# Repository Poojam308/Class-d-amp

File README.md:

# 🔊 Class-D Audio Pre-Amplifier

A specialized hardware design for a high-efficiency Class-D audio pre-amplifier. This project leverages the precision of KiCad 8.0 to implement a switching amplifier topology, focusing on low-noise signal processing and high-frequency pulse-width modulation (PWM).

## **✨ Features**

* **⚡ Class-D Topology:** Utilizes high-frequency switching for superior efficiency compared to traditional linear amplifiers.
* **🎯 Precision Timing:** Employs a CMOS-based LMC555 timer for stable PWM signal generation.
* **📉 Low-Noise Pre-amplification:** Integrated TL072 JFET-input operational amplifiers for high-fidelity audio signal conditioning.
* **🛡️ Robust Power Stage:** Features IRF540N HEXFET Power MOSFETs for reliable switching and power delivery.
* **📏 Compact 2-Layer PCB:** Optimized layout with a small footprint (187.55 mm x 103.05 mm) suitable for various enclosures.

## **🛠️ Design Requirements**

1. **💻 [KiCad 8.0+**](https://www.kicad.org/) (For viewing/modifying schematic and PCB files)
2. **📄 Gerber Viewer** (To inspect manufacturing files)
3. **🔌 12V-24V DC Power Supply** (Recommended for operation)

## **🏗️ Manufacturing Instructions**

### **🖨️ 1. PCB Fabrication**

The `Gerbers/` directory (or the root `.gbr` files) contains everything needed for professional fabrication:

1. **📤 Upload to Fabricator:** Submit the `.gbr` (Gerber) and `.drl` (Drill) files to your preferred PCB manufacturer (e.g., JLCPCB, PCBWay).
2. **⚙️ Stackup Settings:**
* **Layers:** 2
* **Material:** FR4
* **Thickness:** 1.6 mm
* **Copper Weight:** 1oz (standard)

3. **🔍 Solder Mask/Silkscreen:** Standard Green/White (or your preference).

### **🧪 2. Assembly (BOM Highlights)**

* **IC1/IC2:** TL072 (Dual Op-Amp)
* **IC3:** LM311 (Voltage Comparator)
* **IC4:** LMC555 (Timer)
* **Q1-Q4:** BC547/BC557 (Bipolar Junction Transistors)
* **M1:** IRF540N (Power MOSFET)

## **🧠 How It Works**

* **🎙️ Input Stage (`pre audio amplifier.kicad_sch`):** The audio signal enters through the TL072 stages, where it is buffered and amplified to a level suitable for modulation.
* **〰️ PWM Generation:** The LMC555 timer and LM311 comparator work in tandem to convert the analog audio signal into a high-frequency pulse-width modulated (PWM) square wave.
* **🔌 Output Stage:** The modulated signal drives the IRF540N MOSFET, which switches the power supply to the output. This high-frequency signal is then filtered (via external low-pass filter) to reconstruct the amplified audio waveform.
* **📐 PCB Layout:** The `pre audio amplifier.kicad_pcb` uses 0.2mm trace widths and clearances to ensure signal integrity while maintaining a high-density component arrangement.

---

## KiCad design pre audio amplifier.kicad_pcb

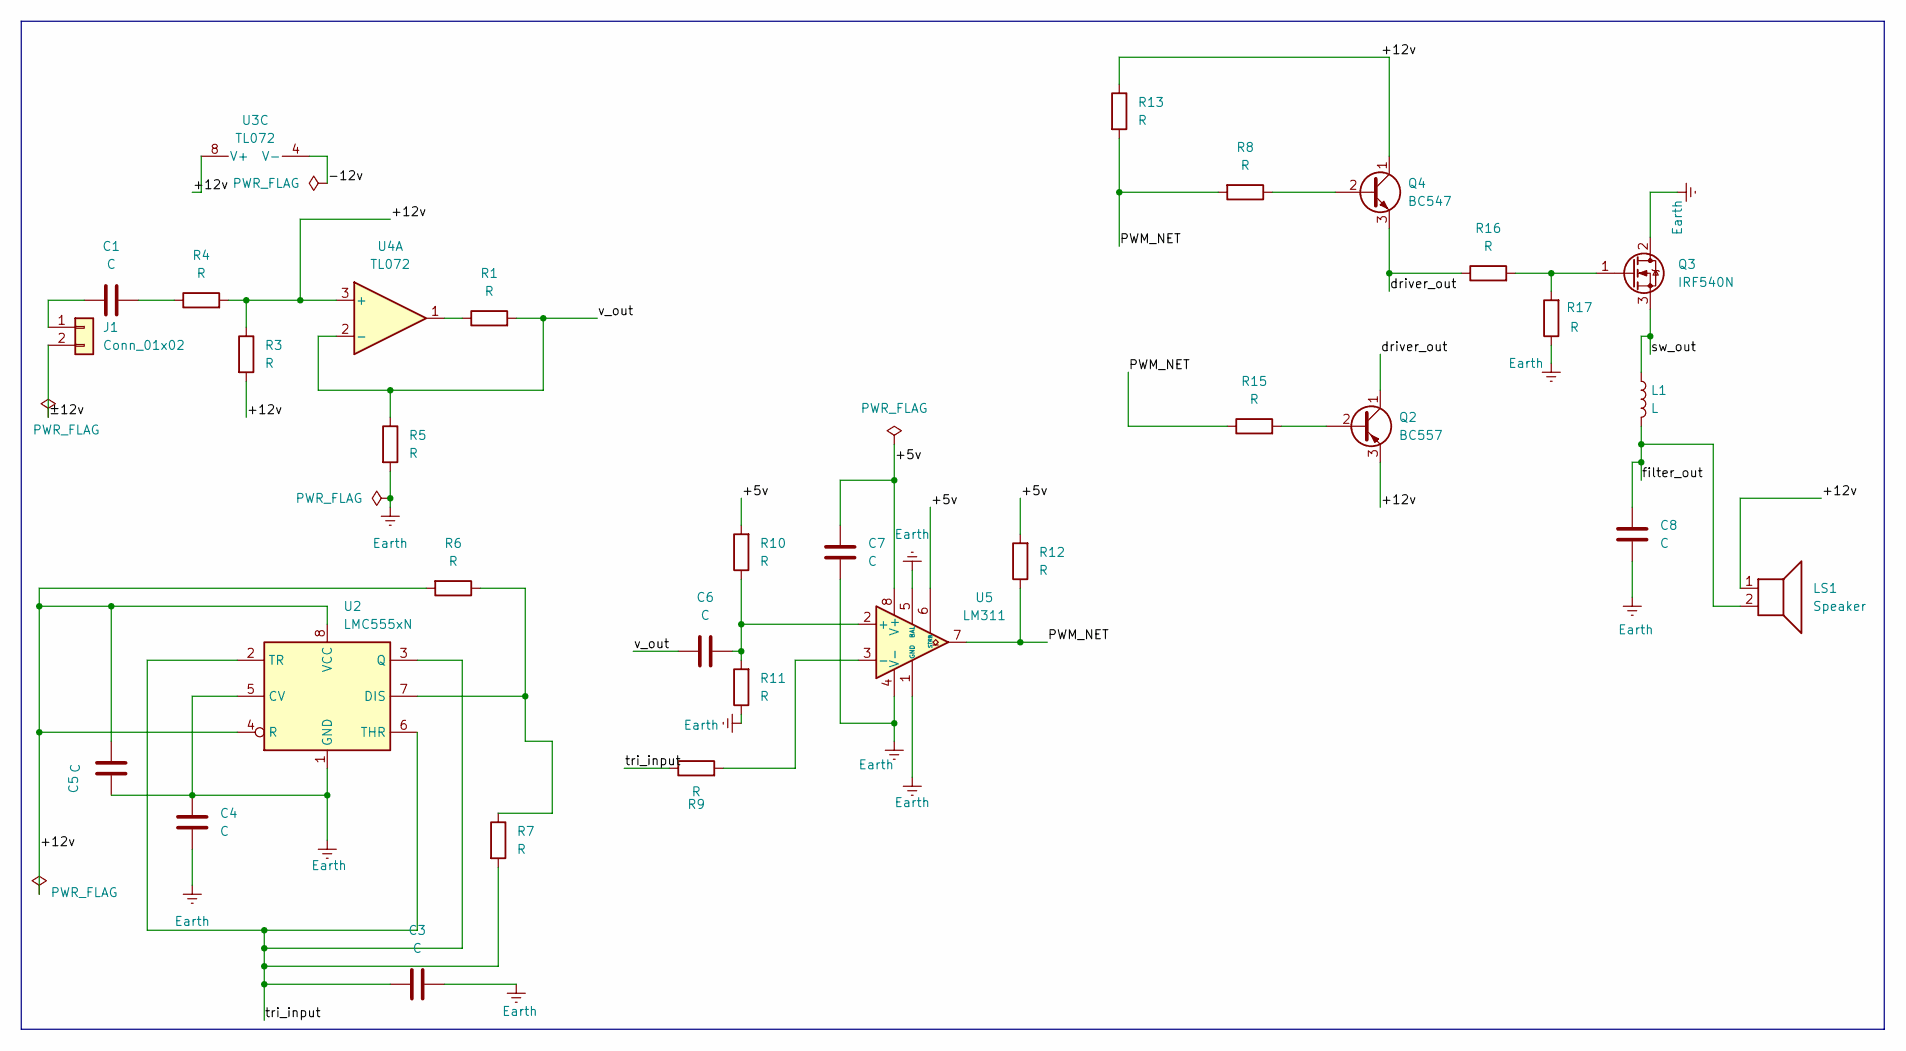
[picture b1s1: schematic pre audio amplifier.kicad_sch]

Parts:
C1, C3, C4, C5, C6, C7, C8: C; CP_Elec_3x5.3
J1: Conn_01x02; JWT_A3963_1x02_P3.96mm_Vertical
L1: L; L_6.3x6.3_H3
LS1: Speaker; Speaker_CUI_CMR-1206S-67
Q2: BC557; TO-92_Inline
Q3: IRF540N; TO-220-3_Vertical
Q4: BC547; TO-92_Inline
R1, R3, R4, R5, R6, R7, R8, R9, R10, R11, R12, R13, R15, R16, R17: R; R_0805_2012Metric
U2: LMC555xN; DIP-8_W7.62mm
U3, U4: TL072; DIP-8-16_W7.62mm_Socket
U5: LM311; DIP-8-16_W7.62mm

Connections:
/+5v: C7.2, R10.2, R12.2, U5.6 (STRB), U5.8 (V+)
/+12v: C5.2, LS1.1, Q2.3 (E), Q4.1 (C), R3.1, R3.2, R4.2, R6.2, R13.1, U2.4 (R), U2.8 (VCC), U3.8 (V+), U4.3 (+)
/-12v: U3.4 (V-)
/PWM_NET: R8.2, R12.1, R13.2, R15.1, U5.7
/driver_out: Q2.1 (C), Q4.3 (E), R16.1
/filter_out: C8.1, L1.2, LS1.2
/sw_out: L1.1, Q3.3 (S)
/tri_input: C3.2, R7.2, R9.1, U2.2 (TR), U2.3 (Q), U2.6 (THR)
/v_out: C6.1, R1.2, R5.1, U4.2 (-)
/±12v: J1.2
Earth: C3.1, C4.1, C4.2, C5.1, C7.1, C8.2, Q3.2 (D), R5.2, R11.1, R17.1, U2.1 (GND), U2.5 (CV), U5.1 (GND), U5.4 (V-), U5.5 (BAL)
unnamed: C1.2, R4.1
unnamed: C1.1, J1.1
unnamed: Q2.2 (B), R15.2
unnamed: Q3.1 (G), R16.2, R17.2
unnamed: Q4.2 (B), R8.1
unnamed: R1.1, U4.1
unnamed: R6.1, R7.1, U2.7 (DIS)
unnamed: C6.2, R10.1, R11.2, U5.2 (+)
unnamed: R9.2, U5.3 (-)

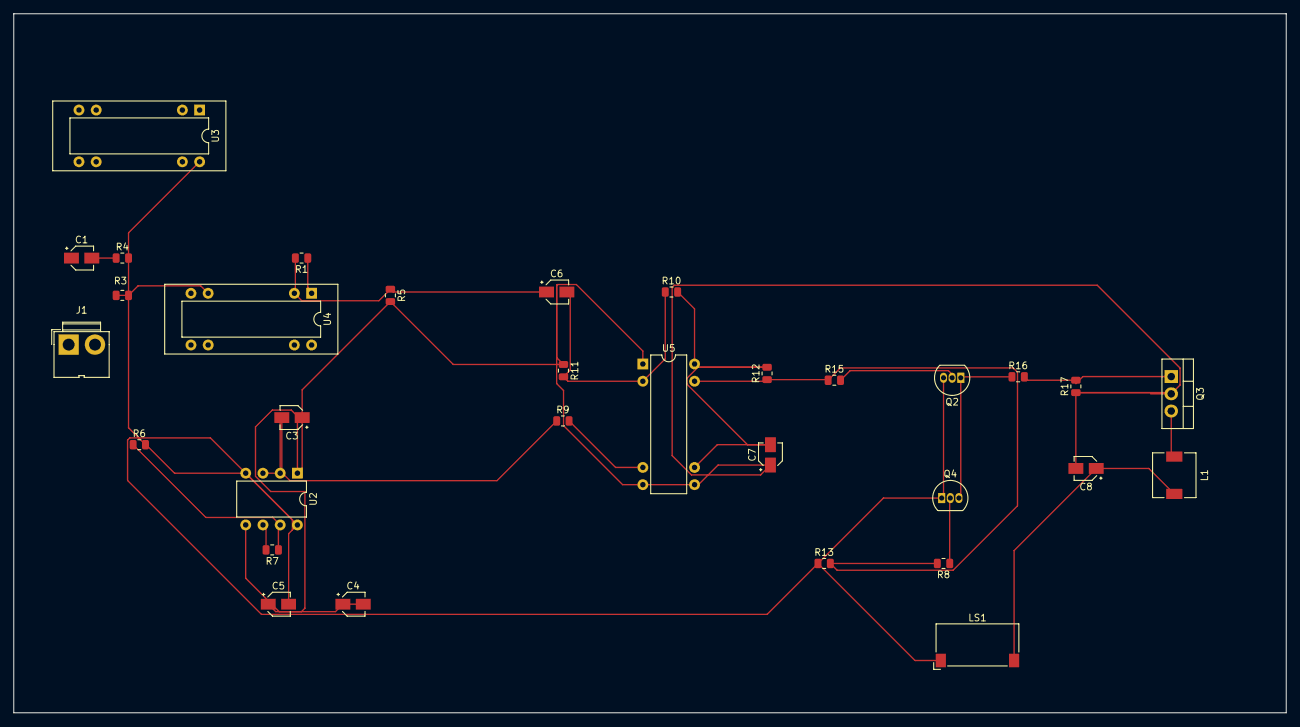
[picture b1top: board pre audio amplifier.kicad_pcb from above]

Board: 2 copper layers, 187.5 x 103.0 mm, 32 parts (0 on the bottom side), 18 nets.
